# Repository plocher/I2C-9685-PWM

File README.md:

# I2C-LEDStripDriver
## License: CERN Open Hardware Licence v1.2

I2C 16 channel PWM Driver based on a PCA9685 

The PCA9685 is an I2C-bus controlled 16-channel LED controller optimized for Red/Green/Blue/Amber (RGBA) color backlighting applications.  It can also be used to control Servos.
Each output has its own 12-bit resolution (4096 steps) fixed frequency individual PWM controller

This design, when used in conjunction with the IO4-LED_STRIP driver board, drives RGB + "white" LED strips - I use one set for backdrop lighting (dawn and dusk sunsets...) and the other for overhead (sunlight) valence illumination.

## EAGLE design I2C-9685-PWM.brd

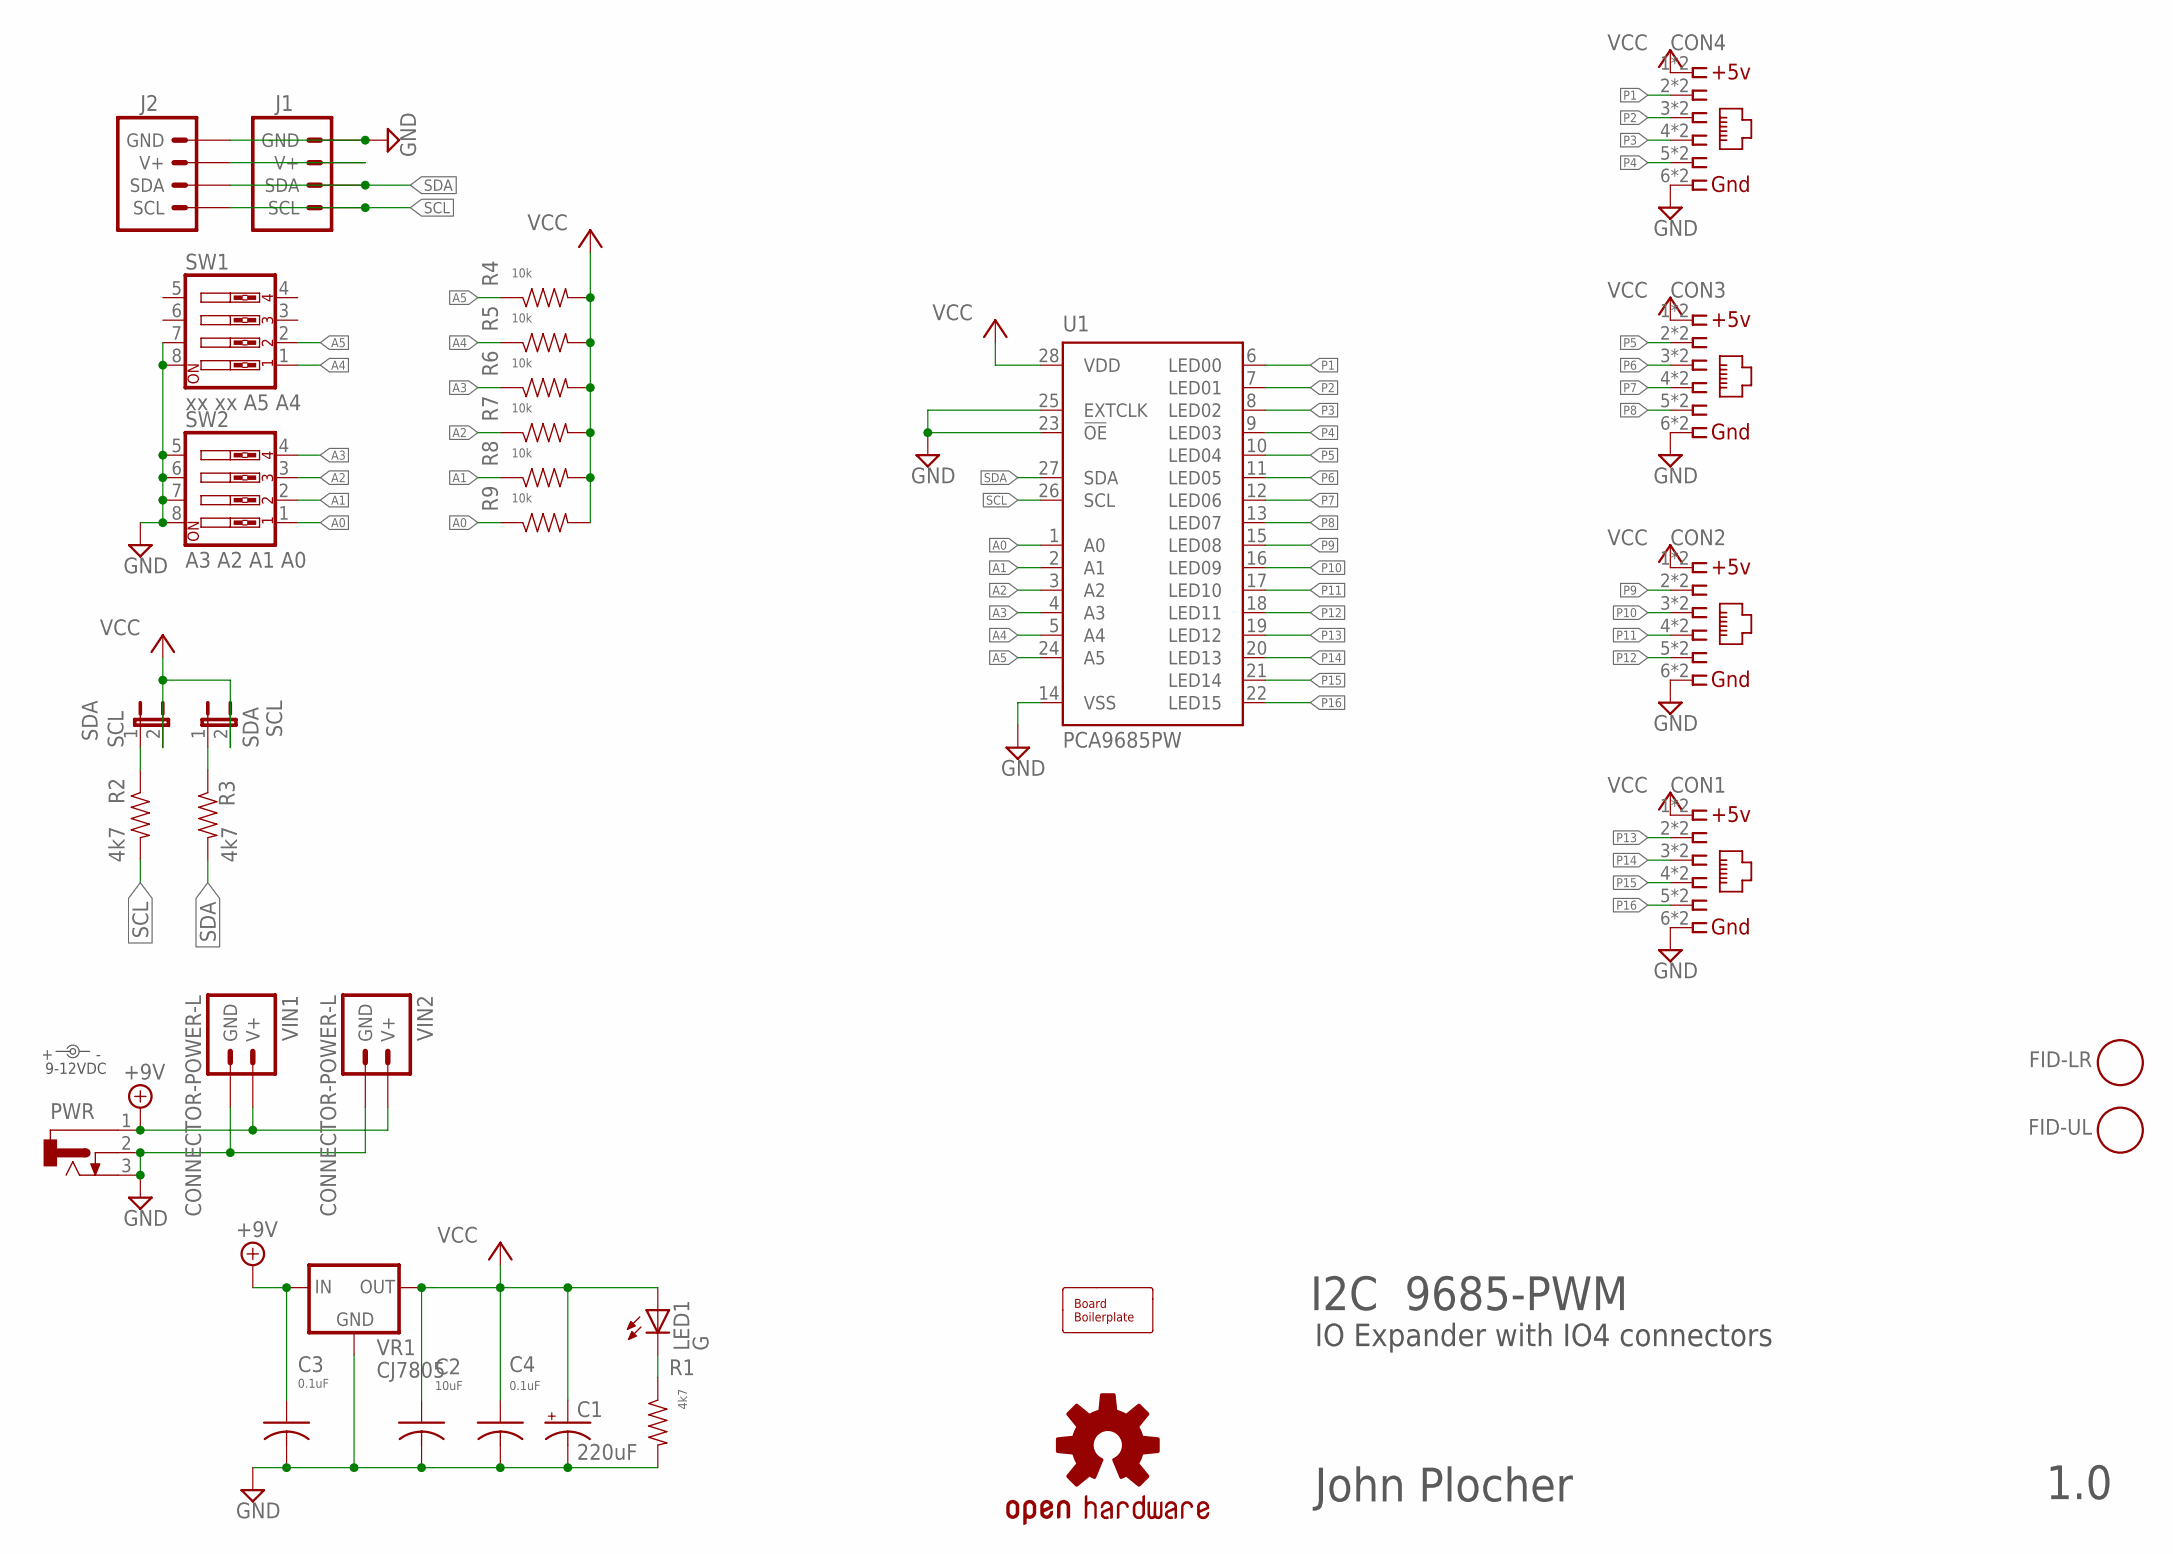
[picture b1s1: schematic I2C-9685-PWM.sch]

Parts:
BOARD1: BOARD80X100-IOB; BOARD-DINRAIL-3.17IN-IOB
C1: 220uF; 0810-CAP
C2: 10uF; 0805-CAP
C3, C4: 0.1uF; 0805-CAP
CON1, CON2, CON3, CON4: CONNECTOR-IO4IPINS; RJ24-INVERTED-PINS
FID-LR: FIDUCIAL; FIDUCIAL_1MM
FID-UL: FIDUCIAL; FIDUCIAL_1MM
J1, J2: CONNECTOR-I2CLEFT; I2C-L
LED1: G; 0603-LED
PWR: CONNECTOR-DC-POWER-RA; DCJ0202
R1, R2, R3: 4k7; 0603-RES
R4, R5, R6, R7, R8, R9: 10k; 0603-RES
SCL: SDA; 1X02_LOCK
SDA: SCL; 1X02_LOCK
SW1: xx xx A5 A4; EDG-04
SW2: A3 A2 A1 A0; EDG-04
U1: PCA9685PW; TSSOP28
U$1: OSHW-LOGOL; OSHW-LOGO-L
VIN: 9-12VDC; PWR_LABEL
VIN1, VIN2: CONNECTOR-POWER-L; POWER-R2
VR1: CJ7805; TO-252

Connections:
+9V: C3.1, PWR.1, VIN1.V+, VIN1.V+@1 (V+), VIN1.V+@2 (V+), VIN1.V+@3 (V+), VIN2.V+, VIN2.V+@1 (V+), VIN2.V+@2 (V+), VIN2.V+@3 (V+), VR1.1 (IN)
A0: R9.1, SW2.1, U1.1 (A0)
A1: R8.1, SW2.2, U1.2 (A1)
A2: R7.1, SW2.3, U1.3 (A2)
A3: R6.1, SW2.4, U1.4 (A3)
A4: R5.1, SW1.1, U1.5 (A4)
A5: R4.1, SW1.2, U1.24 (A5)
GND: C1.-, C2.2, C3.2, C4.2, CON1.6, CON1.6@1 (6), CON2.6, CON2.6@1 (6), CON3.6, CON3.6@1 (6), CON4.6, CON4.6@1 (6), J1.GND, J1.GND@1 (GND), J2.GND, J2.GND@1 (GND), PWR.2, PWR.3, R1.2, SW1.7, SW1.8, SW2.5, SW2.6, SW2.7, SW2.8, U1.14 (VSS), U1.23 (!OE), U1.25 (EXTCLK), VIN1.GND, VIN1.GND@1 (GND), VIN1.GND@2 (GND), VIN1.GND@3 (GND), VIN2.GND, VIN2.GND@1 (GND), VIN2.GND@2 (GND), VIN2.GND@3 (GND), VR1.2 (GND)
unnamed: LED1.C, R1.1
unnamed: R3.1, SCL.1
unnamed: R2.1, SDA.1
P1: CON4.2, CON4.2@1 (2), U1.6 (LED00)
P2: CON4.3, CON4.3@1 (3), U1.7 (LED01)
P3: CON4.4, CON4.4@1 (4), U1.8 (LED02)
P4: CON4.5, CON4.5@1 (5), U1.9 (LED03)
P5: CON3.2, CON3.2@1 (2), U1.10 (LED04)
P6: CON3.3, CON3.3@1 (3), U1.11 (LED05)
P7: CON3.4, CON3.4@1 (4), U1.12 (LED06)
P8: CON3.5, CON3.5@1 (5), U1.13 (LED07)
P9: CON2.2, CON2.2@1 (2), U1.15 (LED08)
P10: CON2.3, CON2.3@1 (3), U1.16 (LED09)
P11: CON2.4, CON2.4@1 (4), U1.17 (LED10)
P12: CON2.5, CON2.5@1 (5), U1.18 (LED11)
P13: CON1.2, CON1.2@1 (2), U1.19 (LED12)
P14: CON1.3, CON1.3@1 (3), U1.20 (LED13)
P15: CON1.4, CON1.4@1 (4), U1.21 (LED14)
P16: CON1.5, CON1.5@1 (5), U1.22 (LED15)
SCL: J1.SCL, J1.SCL@1 (SCL), J2.SCL, J2.SCL@1 (SCL), R2.2, U1.26 (SCL)
SDA: J1.SDA, J1.SDA@1 (SDA), J2.SDA, J2.SDA@1 (SDA), R3.2, U1.27 (SDA)
V+I2C: J1.V+, J1.V+@1 (V+), J2.V+, J2.V+@1 (V+)
VCC: C1.+, C2.1, C4.1, CON1.1, CON1.1@1 (1), CON2.1, CON2.1@1 (1), CON3.1, CON3.1@1 (1), CON4.1, CON4.1@1 (1), LED1.A, R4.2, R5.2, R6.2, R7.2, R8.2, R9.2, SCL.2, SDA.2, U1.28 (VDD), VR1.3 (OUT)

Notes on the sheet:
I2C 9685-PWM
IO Expander with IO4 connectors
John Plocher
1.0

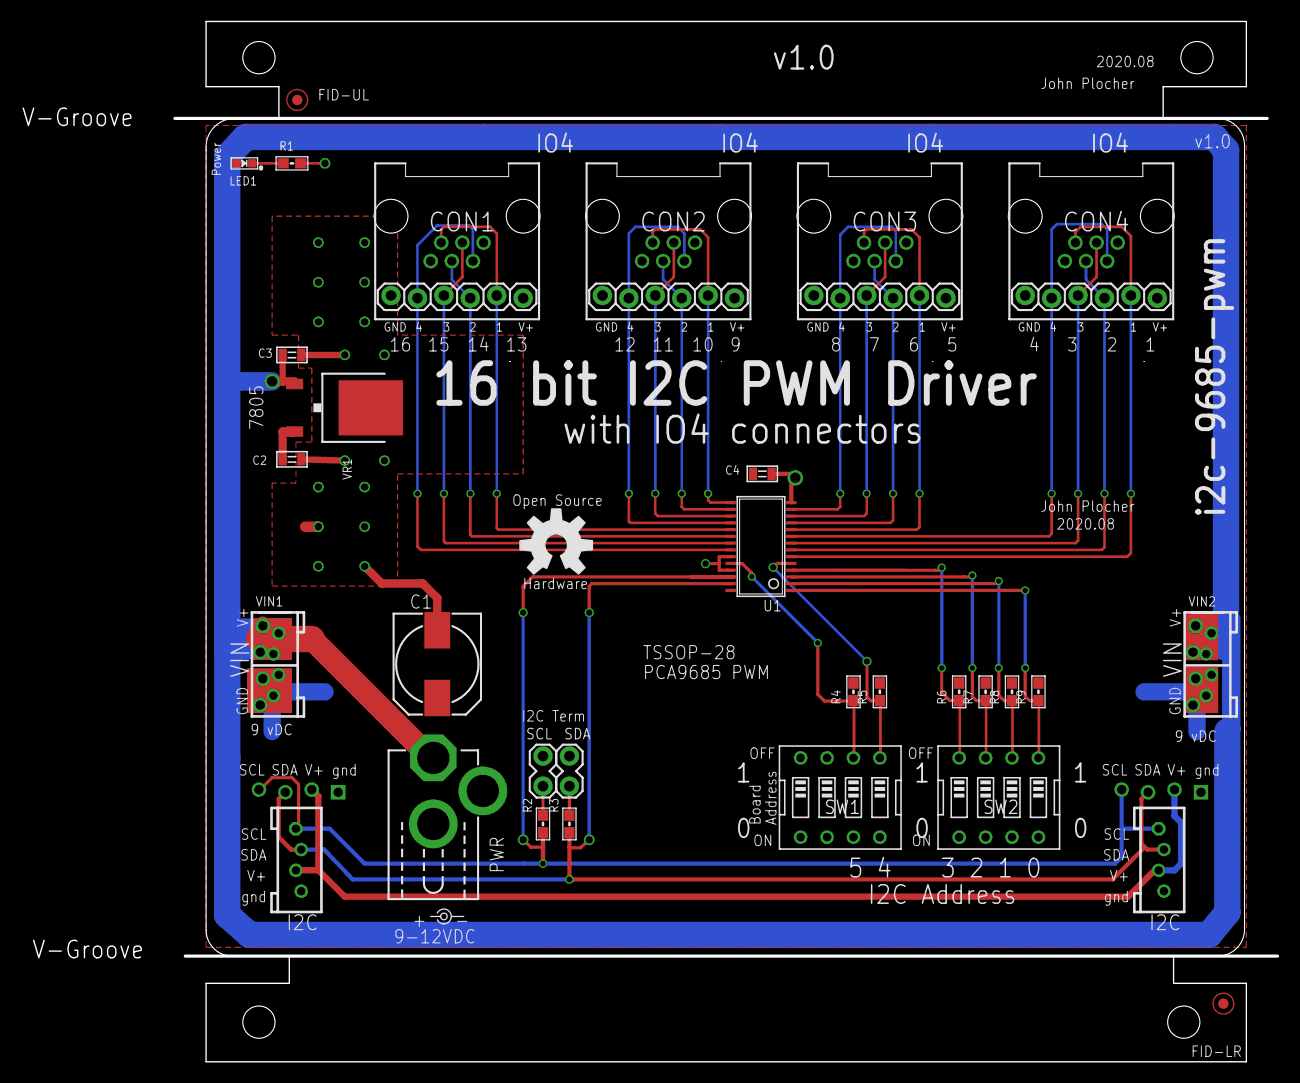
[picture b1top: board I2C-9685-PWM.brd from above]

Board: 2 copper layers, 120.7 x 99.8 mm, 34 parts (0 on the bottom side), 31 nets.

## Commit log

2020-07-28 Initial version
2020-07-28 version#
2020-08-02 RR Tracks on back silk, better ground plane
2020-08-03 better spacing on IO4s and heatsinking on 7805
2020-08-05 fixed SPCoast lbr part orientation
2020-08-12 FID placement & names
